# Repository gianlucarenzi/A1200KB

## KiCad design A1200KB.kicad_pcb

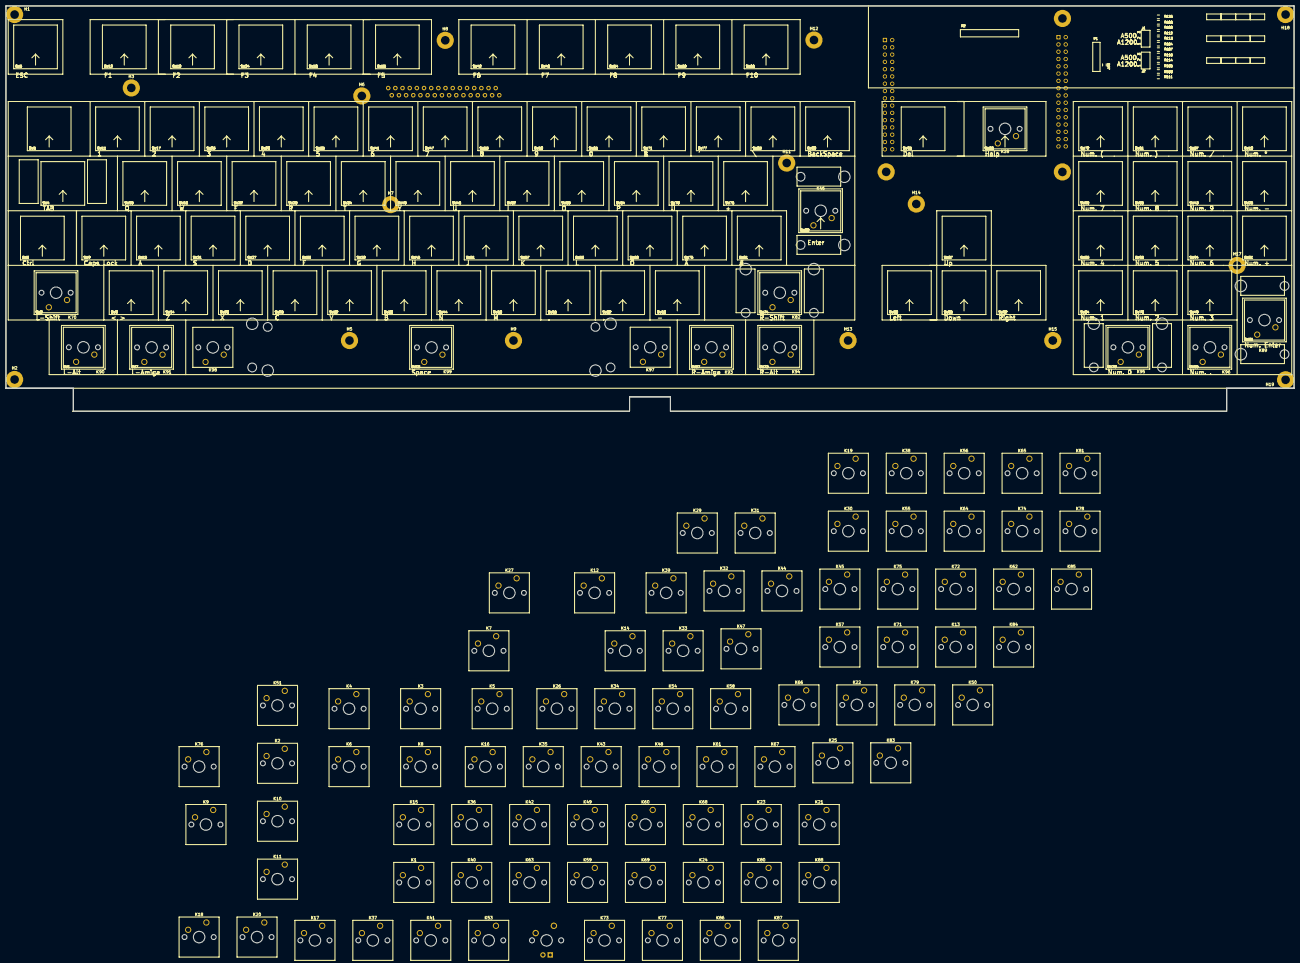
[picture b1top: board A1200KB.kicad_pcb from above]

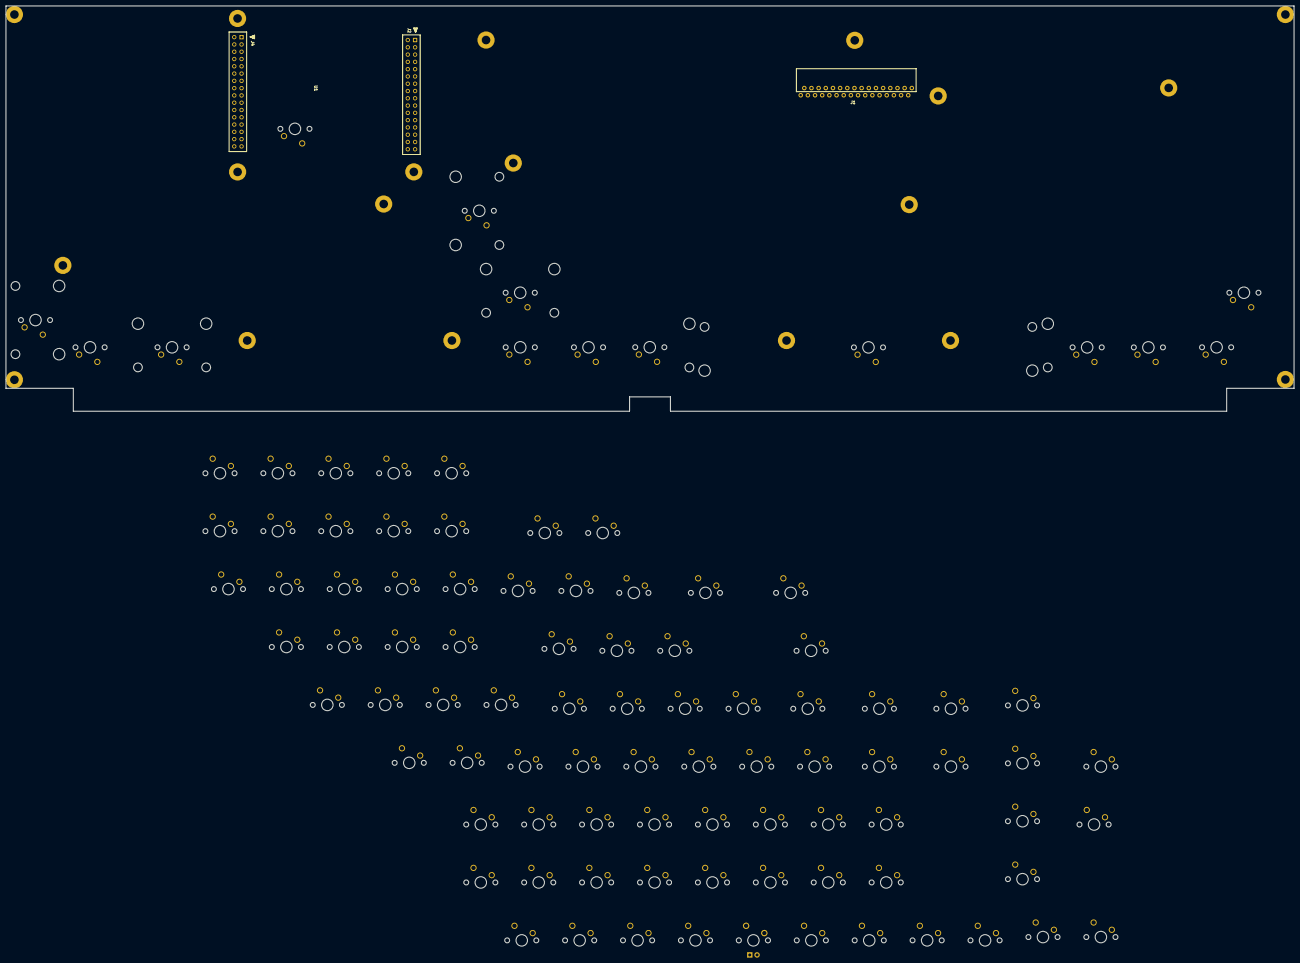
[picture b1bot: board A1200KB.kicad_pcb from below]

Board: 2 copper layers, 449.3 x 141.4 mm, 117 parts (2 on the bottom side), 32 nets, no tracks yet.

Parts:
H1, H2, H3, H5, H6, H7, H8, H9, H11, H12, H13, H14, H15, H17, H18, H19: MountingHole_Pad; MountingHole_3mm_Pad
J1: Conn_01x32_Female; MOLEX-FFC-1.25mm-RA-52044-3245
K1: ESC; SW_Cherry_MX1A_1.00u_PCB_3d
K2: F1; SW_Cherry_MX1A_1.25u_PCB_3d
K3: F2; SW_Cherry_MX1A_1.25u_PCB_3d
K4: F3; SW_Cherry_MX1A_1.25u_PCB_3d
K5: F4; SW_Cherry_MX1A_1.25u_PCB_3d
K6: F5; SW_Cherry_MX1A_1.25u_PCB_3d
K7: F6; SW_Cherry_MX1A_1.25u_PCB_3d
K8: F7; SW_Cherry_MX1A_1.25u_PCB_3d
K9: F8; SW_Cherry_MX1A_1.25u_PCB_3d
K10: F9; SW_Cherry_MX1A_1.25u_PCB_3d
K11: F10; SW_Cherry_MX1A_1.25u_PCB_3d
K12: TILDE; SW_Cherry_MX1A_1.50u_PCB_3d
K13: 1; SW_Cherry_MX1A_1.00u_PCB_3d
K14: 2; SW_Cherry_MX1A_1.00u_PCB_3d
K15: 3; SW_Cherry_MX1A_1.00u_PCB_3d
K16: 4; SW_Cherry_MX1A_1.00u_PCB_3d
K17: 5; SW_Cherry_MX1A_1.00u_PCB_3d
K18: 6; SW_Cherry_MX1A_1.00u_PCB_3d
K19: 7; SW_Cherry_MX1A_1.00u_PCB_3d
K20: 8; SW_Cherry_MX1A_1.00u_PCB_3d
K21: 9; SW_Cherry_MX1A_1.00u_PCB_3d
K22: 0; SW_Cherry_MX1A_1.00u_PCB_3d
K23: MINUS; SW_Cherry_MX1A_1.00u_PCB_3d
K24: PLUS; SW_Cherry_MX1A_1.00u_PCB_3d
K25: PIPE; SW_Cherry_MX1A_1.00u_PCB_3d
K26: BS; SW_Cherry_MX1A_1.00u_PCB_3d
K27: DEL; SW_Cherry_MX1A_1.50u_PCB_3d
K28: HELP; SW_Cherry_MX1A_1.50u_PCB_3d
K29: NUM_(; SW_Cherry_MX1A_1.00u_PCB_3d
K30: NUM_); SW_Cherry_MX1A_1.00u_PCB_3d
K31: NUM_DIV; SW_Cherry_MX1A_1.00u_PCB_3d
K32: NUM_MULT; SW_Cherry_MX1A_1.00u_PCB_3d
K33: TAB; SW_Cherry_MX1A_1.00u_PCB_3d
K34: Q; SW_Cherry_MX1A_1.00u_PCB_3d
K35: W; SW_Cherry_MX1A_1.00u_PCB_3d
K36: E; SW_Cherry_MX1A_1.00u_PCB_3d
K37: R; SW_Cherry_MX1A_1.00u_PCB_3d
K38: T; SW_Cherry_MX1A_1.00u_PCB_3d
K39: Y; SW_Cherry_MX1A_1.00u_PCB_3d
K40: U; SW_Cherry_MX1A_1.00u_PCB_3d
K41: I; SW_Cherry_MX1A_1.00u_PCB_3d
K42: O; SW_Cherry_MX1A_1.00u_PCB_3d
K43: P; SW_Cherry_MX1A_1.00u_PCB_3d
K44: L.CURLY; SW_Cherry_MX1A_1.00u_PCB_3d
K45: R.CURLY; SW_Cherry_MX1A_1.00u_PCB_3d
K46: RETURN; SW_Cherry_MX1A_ISOEnter_Rotated_PCB_3d
K47: NUM_7; SW_Cherry_MX1A_1.00u_PCB_3d
K48: NUM_8; SW_Cherry_MX1A_1.00u_PCB_3d
K49: NUM_9; SW_Cherry_MX1A_1.00u_PCB_3d
K50: NUM_MINUS; SW_Cherry_MX1A_1.00u_PCB_3d
K51: CTRL; SW_Cherry_MX1A_1.25u_PCB_3d
K52: CAPSLOCK; MXOnly-1U
K53: A; SW_Cherry_MX1A_1.00u_PCB_3d
K54: S; SW_Cherry_MX1A_1.00u_PCB_3d
K55: D; SW_Cherry_MX1A_1.00u_PCB_3d
K56: F; SW_Cherry_MX1A_1.00u_PCB_3d
K57: G; SW_Cherry_MX1A_1.00u_PCB_3d
K58: H; SW_Cherry_MX1A_1.00u_PCB_3d
K59: J; SW_Cherry_MX1A_1.00u_PCB_3d
K60: K; SW_Cherry_MX1A_1.00u_PCB_3d
K61: L; SW_Cherry_MX1A_1.00u_PCB_3d
K62: COLON; SW_Cherry_MX1A_1.00u_PCB_3d
K63: "; SW_Cherry_MX1A_1.00u_PCB_3d
K64: R.BLANK; SW_Cherry_MX1A_1.00u_PCB_3d
K65: UP; SW_Cherry_MX1A_1.00u_PCB_3d
K66: NUM_4; SW_Cherry_MX1A_1.00u_PCB_3d
K67: NUM_5; SW_Cherry_MX1A_1.00u_PCB_3d
K68: NUM_6; SW_Cherry_MX1A_1.00u_PCB_3d
K69: NUM_PLUS; SW_Cherry_MX1A_1.00u_PCB_3d
K70: L.SHIFT; SW_Cherry_MX1A_1.75u_PCB_3d
K71: L.BLANK; SW_Cherry_MX1A_1.00u_PCB_3d
K72: Z; SW_Cherry_MX1A_1.00u_PCB_3d
K73: X; SW_Cherry_MX1A_1.00u_PCB_3d
K74: C; SW_Cherry_MX1A_1.00u_PCB_3d
K75: V; SW_Cherry_MX1A_1.00u_PCB_3d
K76: B; SW_Cherry_MX1A_1.00u_PCB_3d
K77: N; SW_Cherry_MX1A_1.00u_PCB_3d
K78: M; SW_Cherry_MX1A_1.00u_PCB_3d
K79: R.CROC; SW_Cherry_MX1A_1.00u_PCB_3d
K80: L.CROC; SW_Cherry_MX1A_1.00u_PCB_3d
K81: QUESTION; SW_Cherry_MX1A_1.00u_PCB_3d
K82: R.SHIFT; SW_Cherry_MX1A_2.75u_PCB_3d
K83: LEFT; SW_Cherry_MX1A_1.00u_PCB_3d
K84: DOWN; SW_Cherry_MX1A_1.00u_PCB_3d
K85: RIGHT; SW_Cherry_MX1A_1.00u_PCB_3d
K86: NUM_1; SW_Cherry_MX1A_1.00u_PCB_3d
K87: NUM_2; SW_Cherry_MX1A_1.00u_PCB_3d
K88: NUM_3; SW_Cherry_MX1A_1.00u_PCB_3d
K89: NUM_ENTER; SW_Cherry_MX1A_2.00u_Vertical_PCB_3d
K90: L.ALT; SW_Cherry_MX1A_1.25u_PCB_3d
K91: L.AMIGA; SW_Cherry_MX1A_1.25u_PCB_3d
K92: SPACE 7U; MXOnly-7U-NoSwitch
K93: R.AMIGA; SW_Cherry_MX1A_1.25u_PCB_3d
K94: R.ALT; SW_Cherry_MX1A_1.25u_PCB_3d
K95: NUM_0; SW_Cherry_MX1A_2.00u_PCB_3d
K96: NUM_DECIMAL; SW_Cherry_MX1A_1.00u_PCB_3d
K97: MENU; SW_Cherry_MX1A_1.00u_PCB_3d
K98: SUPER; SW_Cherry_MX1A_1.00u_PCB_3d
K99: SPACE 9U; SW_Cherry_MX1A_9u_PCB_3d
U1: STM32F401-DK

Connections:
/1: J1.1, K33.1, K34.2, K35.2, K36.2, K37.2, K38.2, K39.1, K40.2, K41.2, K42.2, K43.2, K44.2, K45.2, K46.1, K83.2
/2: J1.2, K27.2, K52.2, K53.2, K54.2, K55.2, K56.2, K57.2, K58.1, K59.2, K60.2, K61.2, K62.2, K63.2, K64.2, K85.2
/3: J1.3, K26.2, K71.2, K72.2, K73.2, K74.2, K75.2, K76.2, K77.1, K78.2, K79.2, K80.2, K81.2, K84.1, K97.2, K98.1, K98.2, K99.2
/4: J1.4, K32.2, K47.2, K48.2, K49.2, K50.2, K66.2, K67.2, K68.2, K69.2, K86.2, K87.2, K88.2, K89.2, K95.1, K96.2
/5: J1.5, K12.2, K13.2, K14.2, K15.2, K16.2, K17.2, K18.1, K19.2, K20.1, K21.2, K22.2, K23.2, K24.2, K25.1, K65.1
/6: J1.6, K82.1
/7: J1.7, K1.2, K2.2, K3.2, K4.2, K5.2, K6.2, K7.1, K8.2, K9.2, K10.2, K11.2, K28.2, K29.2, K30.2, K31.2
/8: J1.8, K94.1
/9: J1.9, K52.3
/10: J1.10, K93.2
/11: J1.11, K51.2
/12: J1.12, K70.2
/13: J1.13, K90.2
/14: J1.14, K91.2
/15: J1.15, K1.1, K12.1, K32.1, K33.2, K52.1, K71.1
/16: J1.16, K13.1, K29.1, K34.1, K53.1, K69.1, K72.1
/17: J1.17, K2.1, K14.1, K35.1, K49.1, K54.1, K73.1
/18: J1.18, K3.1, K15.1, K36.1, K55.1, K68.1, K74.1
/19: J1.19, K4.1, K16.1, K37.1, K56.1, K75.1, K88.1
/20: J1.20, K5.1, K17.1, K38.1, K57.1, K76.1, K96.1
/21: J1.21, K6.1, K18.2, K39.2, K48.1, K58.2, K77.2
/22: J1.22, K19.1, K30.1, K40.1, K59.1, K67.1, K78.1
/23: J1.23, K7.2, K20.2, K41.1, K60.1, K79.1, K87.1
/24: J1.24, K21.1, K31.1, K42.1, K61.1, K80.1, K89.1
/25: J1.25, K8.1, K22.1, K43.1, K47.1, K62.1, K81.1
/26: J1.26, K9.1, K23.1, K44.1, K63.1, K66.1
/27: J1.27, K10.1, K24.1, K45.1, K64.1, K86.1, K97.1, K99.1
/28: J1.28, K11.1, K25.2, K26.1, K27.1, K46.2, K95.2
/29: J1.29, K28.1, K50.1, K65.2, K83.1, K84.2, K85.1
/30: J1.30, K51.1, K70.1, K82.2, K90.1, K91.1, K93.1, K94.2
/31: J1.31, K52.4
GND: H1.1, H2.1, H3.1, H5.1, H6.1, H7.1, H8.1, H9.1, H11.1, H12.1, H13.1, H14.1, H15.1, H17.1, H18.1, H19.1

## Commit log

2020-11-22 First Attempt to use online tools for holes and PCB keyset placement.
2020-11-22 Color changed from brown/beige to grey for modifiers (more common) and increased some font size.
2020-11-23 Added layers for size, legends, etc.,...
2020-11-26 Image for AliExpress
2020-11-26 Almost complete: arrow keys and backspace, Amiga Keys, Return ISO Key and TAB key missing.
2020-11-27 The size of the font in the upper left corner of the keyboard is increased a little bit
2020-11-30 Added Amiga Keys and other semi graphics symbols. All fonts converted to Helvetica Neue
2020-12-01 Increased the size of the arrow a little bit. Enter key is more like Amiga 4000 keyboard
2020-12-01 Bigger arrows. Bigger Enter key
2021-03-04 Reduced modifiers font size from 11.0pt to 10.pt. Both shift keys have the arrow legend and _NOT_ the "Shift" lettering.
2022-01-12 Build ignored
2022-01-12 New spacebar layout. 7u + 1u + 1u
2022-01-13 Removed
2022-01-13 Not needed
2022-01-13 Imported from Altium
2022-01-13 Now has the AmigaComponents.lib dependancy
2022-01-14 The ISO Enter here, must have rotated Cherry MX switch by 180 degrees
2022-01-15 Added MCU controller sheet page
2022-01-17 Added the autogenerated plate by http://builder.swillkb.com/
2022-01-17 for 7U spacebar
2022-01-17 This should be used to align on the custom keyboard case. It works even for building a plate for original Amiga case. The plate should be laser cutted and folded to match the original plastic case ho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
2022-01-18 Amiga Layout with bigass Enter key
2022-01-20 First import from ATARI KEYBOARD CONTROLLER
2022-01-20 First AUTOGEN project. Must be completed
2022-01-21 Updated with all used pins
2022-01-21 First attempt to drive Amiga Keyboard pins
2022-01-22 Optimized. Must be tried on real Amiga Hardware
2022-01-22 Optimized. Static functions first, then globals
2022-01-22 Custom 8 timers added. Must be checked on real hardware
2022-01-22 LED_POWER Added (PA4)
2022-01-22 Added POWER LED
2022-05-04 Font adapted after Waterslides
2022-05-04 Updated for DSA Style Keycaps
2022-06-12 Printed 4 keycaps (31 USD each + shipping 8 USD each + import tax 30%) Changsha Kuangkuang Technology Co., Ltd.
2022-06-12 Reduced legend sizes for letters and for numbers (KP and ROW 1) Added all PC ISO/ANSI Sizes for a complete USB Amiga Replacement keyboard keycaps
2022-06-14 Updated ROWS information
2022-07-06 Removed STM32F401_DK from Page #1. It will be included in the page #2 MCU
2022-07-06 Added some global netlist
2022-07-13 All fonts are vectors
2022-07-13 Proposed correction
2022-07-13 Added two extra Caps Lock keycaps for the wrong ones in the previous dyesub. Added extra arrow keys to complete all sets.
2022-07-14 Updated COLORS layer for GREY. The KEYBOARD layer is now locked by default.
2022-10-28 Added PANTONE COLORS Fix Scroll Lock. It was Screen Lock
2022-10-31 Amiga CDTV or CD32 Black Keyboard
2022-11-12 Added 4 keycaps: "2, pound 3, #@ and a colored | \ for better compatibility with other layouts
2022-11-15 The pound sign is a little smaller. It looks better to me, now.
2022-11-18 White keycaps are now: PANTONE 179-1U
2022-12-27 Added 3 keys: 1.5U Code, 2 blank keys 1.50U and 1.25U
2022-12-28 Added \| in multicolor mode. Added 1.25U and 1.50U in white and color (7U issue)
2022-12-29 Added full KLE
2023-01-10 PDFs
2023-01-15 Mechanical MOLD for three prints (AFLION)
2023-01-16 Re-arranged layout to keep the production of keycaps simpler.
2023-01-21 File renamed
2023-01-21 Deleted because it causes illegal filenames on my systems
2023-02-16 Added the correct molds for XDA profile (139 keys) :-(
2023-02-18 LED on PA0 (GND Active)
2023-02-18 Added
2023-02-18 Clean up
2023-02-18 Renamed (lowercase)
2023-02-18 new syscall api
2023-02-18 lowercase
2023-02-18 new API
2023-02-18 GNU Linker script ready for bootloader/eeprom sim
2023-02-18 Commodore Braunschweig Amiga VID & PID based on Zorro IDs ;-)
2023-02-18 Only Amiga
2023-02-18 Ported from latest STALKER
2023-02-19 Updated from AEBERBACH GitHub repo
2023-02-19 Added comment
2023-02-19 If it is found an Amiga Reset, the protocol will be reinitialized as well. It is a RESET if it is more than 300 msec (maybe 500 or more)
2023-02-19 amiga_protocol_is_reset() is defined now static. It is called by an __weak function hook_keyboard_loop(), so there is no need to keep it global
2023-03-25 Update to 6.8.0 STM32CubeMX
2024-11-04 Updated with the correct keystroke couple
2025-11-01 RetroBitLab library
2025-11-18 Update ST Library
2025-11-18 Added FreeRTOS support
2025-11-18 First test to separate tasks
2025-11-18 Added serial print debugger task.
2025-11-18 CMSIS OS V2
2025-11-18 OS aware timings
2025-11-18 HAL_TIM_PeriodElapsedCallback missing
2025-11-18 non necessari
2025-11-18 CubeMX update and IOC updated
2025-11-18 When in output mode PULLUP enable. The protocol says the data are valid when low
2025-11-18 PC1 is used as BOOT_MODE PD2 is used as COL1
2025-11-19 Cleanup
2025-11-19 Added macros for numeric keypad open/close parenthesis
2025-11-19 eye candy
2025-11-19 KEY_HELP can be used
2025-11-19 Optimized
2025-11-19 Updated layout
2025-11-19 New keyboard layout for columns and rows
2025-11-19 Updated from latest libraries from ST
2025-11-19 Gestione led RGB su PA1
2025-11-19 Si usano le macro in main.h
2025-11-19 All hardcoded clock and frequency macros in amiga_usb_mx/Core/Src/ws2812.c have been replaced with dynamic calculations using ST HAL library functions, ensuring that the WS2812B timings adapt to the 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
2025-11-19 Better readability
2025-11-21 Added by CubeMX for FreeRTOS
2025-11-21 Modified by CubeMX for FreeRTOS
2025-11-21 Ignore build directory
2025-11-21 Bootloader NEEDED
2025-11-21 Added queues
2025-11-21 The printf is managed by a queue/task
2025-11-21 Added debug messages
2025-11-21 Python scancode/keyboard matrix generator
2025-11-21 The keyboard layout is in a separate file
2025-11-21 Corretto layout
2025-11-21 Gestione led ws2812 (1 led)
